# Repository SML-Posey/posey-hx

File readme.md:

# Posey Hub Platform

This is a simple IMU hardware platform sized to fit in a waist-mounted device. The hub unit operates as both an IMU and a data collection device, connecting to other Posey devices and logging their data to on-board flash.

It includes:

- nRF5340 ARM microtroller with BLE radio
- CEVA BNO086 9-axis IMU
- Flash
- Lithium-polymer operation and charging

## Author

[Anthony Wertz](https://me.anthonywertz.com)

## License

Shield: [![CC BY-SA 4.0][cc-by-sa-shield]][cc-by-sa]

This work is licensed under a
[Creative Commons Attribution-ShareAlike 4.0 International License][cc-by-sa].

[![CC BY-SA 4.0][cc-by-sa-image]][cc-by-sa]

[cc-by-sa]: http://creativecommons.org/licenses/by-sa/4.0/
[cc-by-sa-image]: https://licensebuttons.net/l/by-sa/4.0/88x31.png
[cc-by-sa-shield]: https://img.shields.io/badge/License-CC%20BY--SA%204.0-lightgrey.svg

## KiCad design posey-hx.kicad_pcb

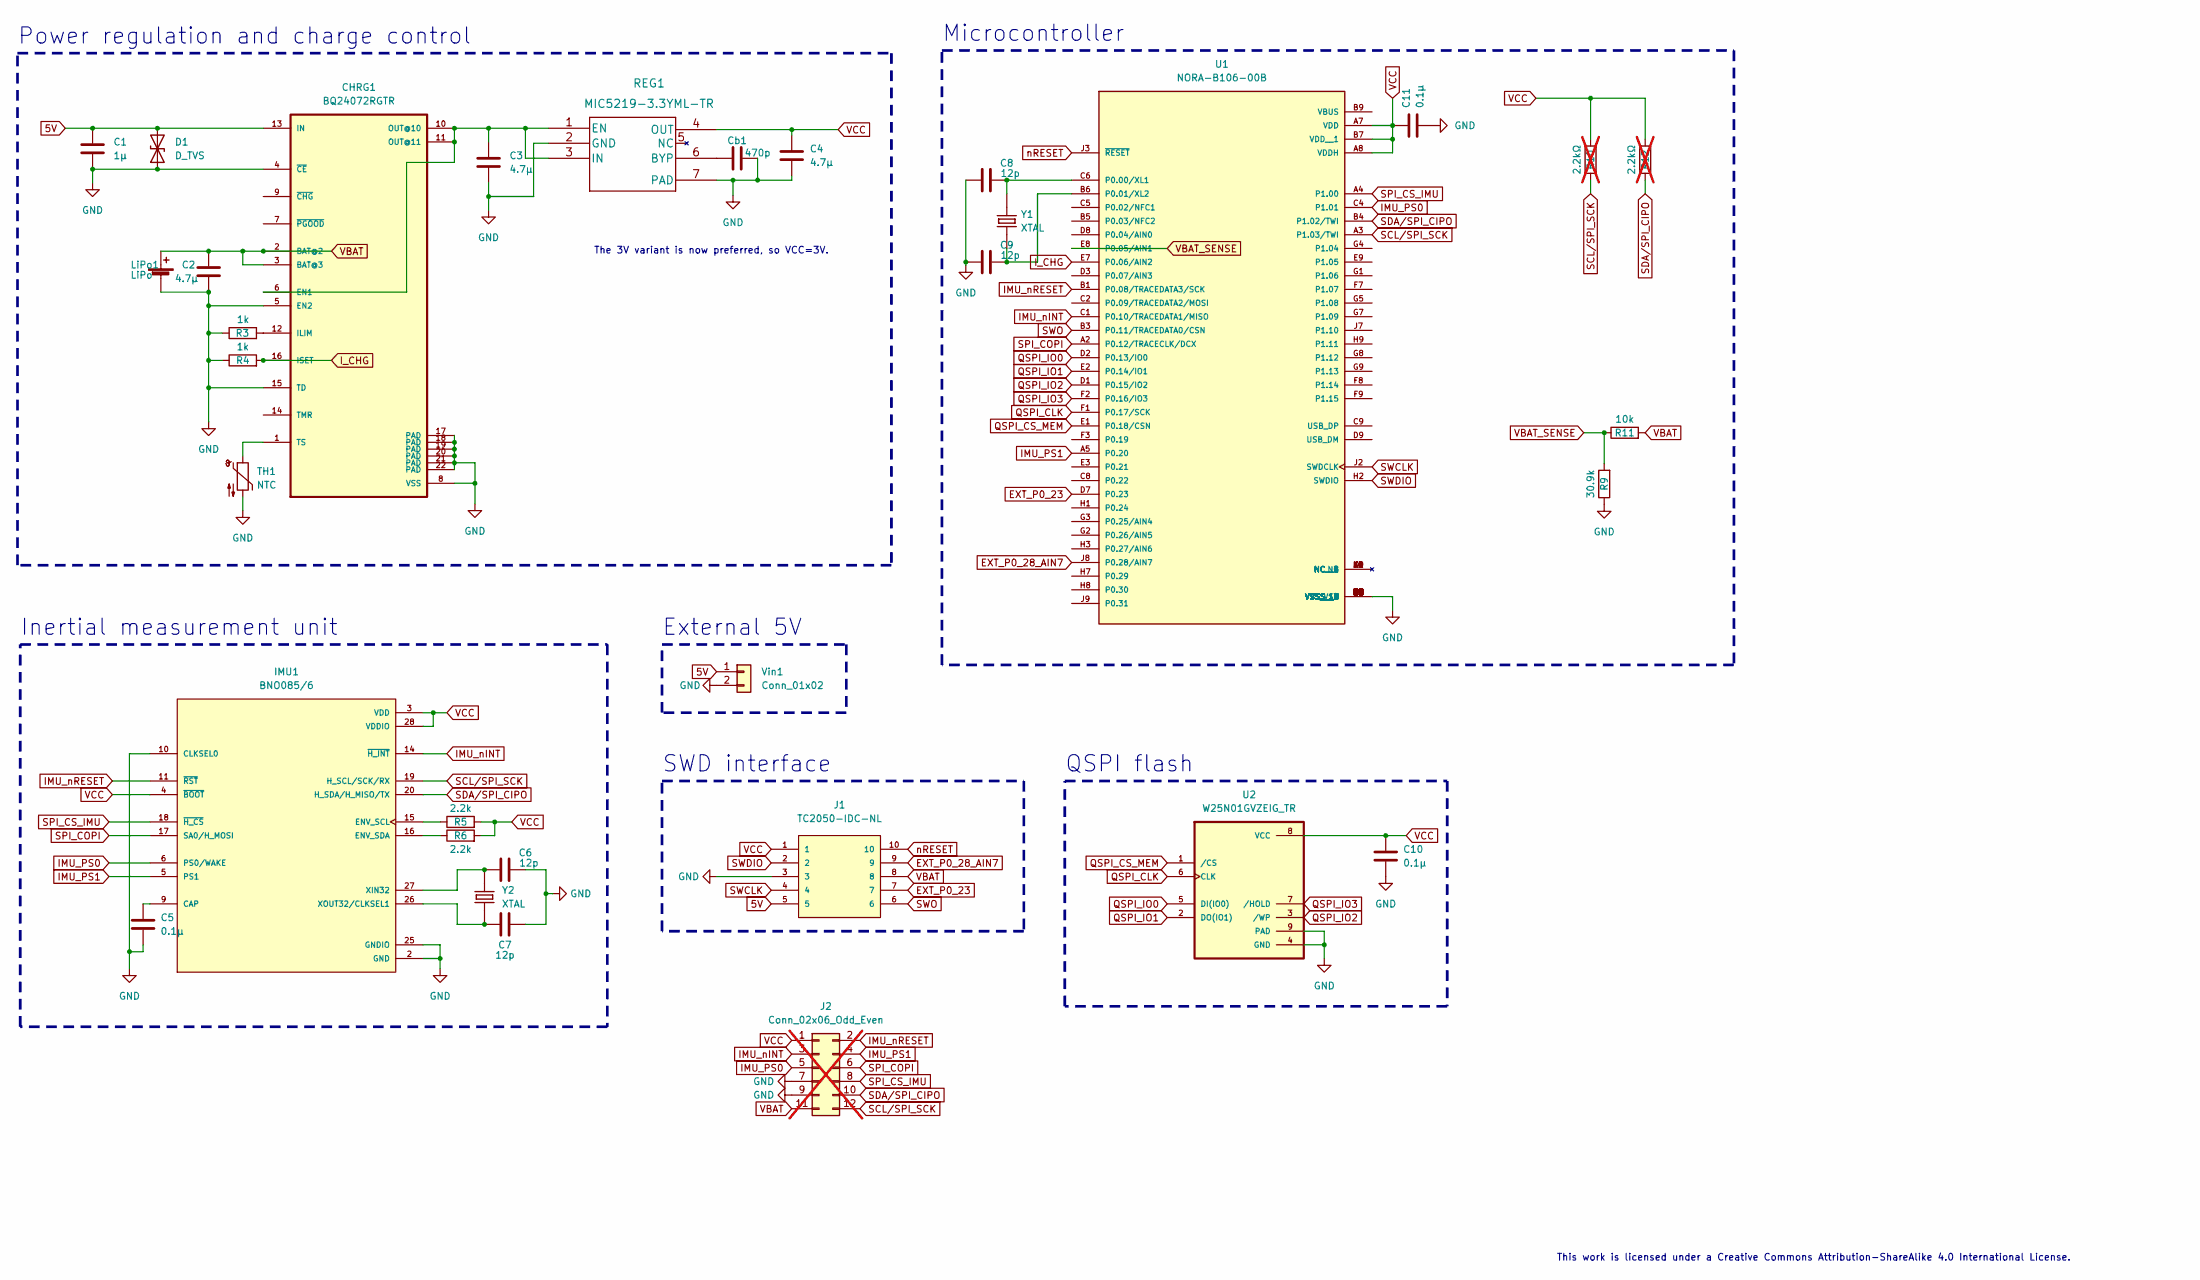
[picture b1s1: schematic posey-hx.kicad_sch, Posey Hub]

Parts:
C1: 1µ; C_0402_1005Metric
C2, C3, C4: 4.7µ; C_0402_1005Metric
C5, C10, C11: 0.1µ; C_0402_1005Metric
C6, C7, C8, C9: 12p; C_0402_1005Metric
CHRG1: BQ24072RGTR; QFN50P300X300X100-17N
Cb1: 470p; C_0402_1005Metric
D1: D_TVS; D_0402_1005Metric
IMU1: BNO085/6; IC_BNO080
J1: TC2050-IDC-NL
J2: Conn_02x06_Odd_Even; PinHeader_2x06_P1.27mm_Vertical; not fitted
LiPo1: LiPo; Split Terminal 2.54
R3, R4: 1k; R_0402_1005Metric
R5, R6: 2.2k; R_0402_1005Metric
R9: 30.9k; R_0402_1005Metric
R10, R12: 2.2kΩ; R_0402_1005Metric; not fitted
R11: 10k; R_0402_1005Metric
REG1: MIC5219-3.3YML-TR
TH1: NTC; R_0402_1005Metric
U1: NORA-B106-00B; XCVR_NORA-B106-00B
U2: W25N01GVZEIG_TR; SON127P800X600X80-9N
Vin1: Conn_01x02; Split Terminal 2.54
Y1, Y2: XTAL; XTAL_ECS-.327-9-16-TR

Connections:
5V: C1.1, CHRG1.13 (IN), D1.2 (A2), J1.5, Vin1.1
EXT_P0_23: J1.7, U1.D7 (P0.23)
EXT_P0_28_AIN7: J1.9, U1.J8 (P0.28/AIN7)
GND: C1.2, C2.1, C3.2, C4.2, C5.2, C6.2, C7.2, C8.1, C9.1, C10.2, C11.2, CHRG1.4 (~CE), CHRG1.5 (EN2), CHRG1.8 (VSS), CHRG1.15 (TD), CHRG1.17 (PAD), CHRG1.18 (PAD), CHRG1.19 (PAD), CHRG1.20 (PAD), CHRG1.21 (PAD), CHRG1.22 (PAD), Cb1.2, D1.1 (A1), IMU1.2 (GND), IMU1.10 (CLKSEL0), IMU1.25 (GNDIO), J1.3, J2.7, J2.9, LiPo1.2 (-), R3.1, R4.1, R9.1, REG1.2 (GND), REG1.7 (PAD), TH1.2, U1.A1 (VSS), U1.A9 (VSS__1), U1.B2 (VSS__2), U1.B8 (VSS__3), U1.E4 (VSS__4), U1.E5 (VSS__5), U1.F4 (VSS__6), U1.F5 (VSS__7), U1.K2 (VSS__8), U1.K3 (VSS__9), U1.K5 (VSS__10), U1.K7 (VSS__11), U1.K8 (VSS__12), U1.L1 (VSS__13), U1.L9 (VSS__14), U1.M1 (VSS__15), U1.M2 (VSS__16), U1.M8 (VSS__17), U1.M9 (VSS__18), U2.4 (GND), U2.9 (PAD), Vin1.2
IMU_PS0: IMU1.6 (PS0/WAKE), J2.5, U1.C4 (P1.01)
IMU_PS1: IMU1.5 (PS1), J2.4, U1.A5 (P0.20)
IMU_nINT: IMU1.14 (~H_INT), J2.3, U1.C1 (P0.10/TRACEDATA1/MISO)
IMU_nRESET: IMU1.11 (~RST), J2.2, U1.B1 (P0.08/TRACEDATA3/SCK)
I_CHG: CHRG1.16 (ISET), R4.2, U1.E7 (P0.06/AIN2)
unnamed: C3.1, CHRG1.6 (EN1), CHRG1.10 (OUT@10), CHRG1.11 (OUT@11), REG1.1 (EN), REG1.3 (IN)
unnamed: CHRG1.12 (ILIM), R3.2
unnamed: CHRG1.1 (TS), TH1.1
unnamed: C5.1, IMU1.9 (CAP)
unnamed: IMU1.15 (ENV_SCL), R5.1
unnamed: IMU1.16 (ENV_SDA), R6.1
unnamed: C6.1, IMU1.27 (XIN32), Y2.2
unnamed: C7.1, IMU1.26 (XOUT32/CLKSEL1), Y2.1
unnamed: Cb1.1, REG1.6 (BYP)
unnamed: C8.2, U1.C6 (P0.00/XL1), Y1.1
unnamed: C9.2, U1.B6 (P0.01/XL2), Y1.2
QSPI_CLK: U1.F1 (P0.17/SCK), U2.6 (CLK)
QSPI_CS_MEM: U1.E1 (P0.18/CSN), U2.1 (/CS)
QSPI_IO0: U1.D2 (P0.13/IO0), U2.5 (DI(IO0))
QSPI_IO1: U1.E2 (P0.14/IO1), U2.2 (DO(IO1))
QSPI_IO2: U1.D1 (P0.15/IO2), U2.3 (/WP)
QSPI_IO3: U1.F2 (P0.16/IO3), U2.7 (/HOLD)
SCL/SPI_SCK: IMU1.19 (H_SCL/SCK/RX), J2.12, R10.1, U1.A3 (P1.03/TWI)
SDA/SPI_CIPO: IMU1.20 (H_SDA/H_MISO/TX), J2.10, R12.1, U1.B4 (P1.02/TWI)
SPI_COPI: IMU1.17 (SA0/H_MOSI), J2.6, U1.A2 (P0.12/TRACECLK/DCX)
SPI_CS_IMU: IMU1.18 (~H_CS), J2.8, U1.A4 (P1.00)
SWCLK: J1.4, U1.J2 (SWDCLK)
SWDIO: J1.2, U1.H2 (SWDIO)
SWO: J1.6, U1.B3 (P0.11/TRACEDATA0/CSN)
VBAT: C2.2, CHRG1.2 (BAT@2), CHRG1.3 (BAT@3), J1.8, J2.11, LiPo1.1 (+), R11.2
VBAT_SENSE: R9.2, R11.1, U1.E8 (P0.05/AIN1)
VCC: C4.1, C10.1, C11.1, IMU1.3 (VDD), IMU1.4 (~BOOT), IMU1.28 (VDDIO), J1.1, J2.1, R5.2, R6.2, R10.2, R12.2, REG1.4 (OUT), U1.A7 (VDD), U1.A8 (VDDH), U1.B7 (VDD__1), U2.8 (VCC)
nRESET: J1.10, U1.J3 (~RESET)

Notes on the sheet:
Power regulation and charge control
Microcontroller
External 5V
The 3V variant is now preferred, so VCC=3V.
Inertial measurement unit
This work is licensed under a Creative Commons Attribution-ShareAlike 4.0 International License.
SWD interface
QSPI flash

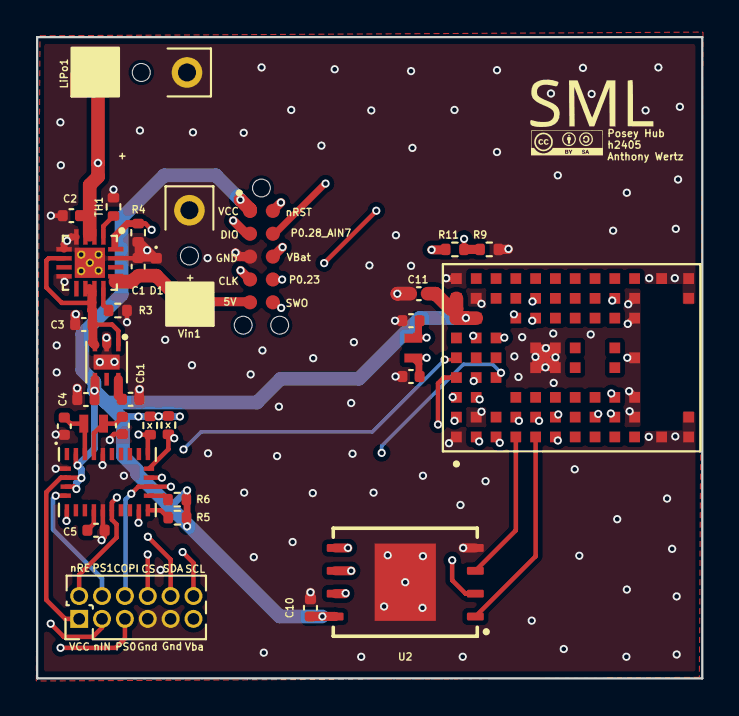
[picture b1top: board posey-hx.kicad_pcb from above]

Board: 4 copper layers, 37.0 x 35.6 mm, 33 parts (0 on the bottom side), 37 nets.

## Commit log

2023-10-25 Initial
2023-10-25 h2310
2024-07-01 Updated readme, license, and version.
2024-07-01 Updated readme.
